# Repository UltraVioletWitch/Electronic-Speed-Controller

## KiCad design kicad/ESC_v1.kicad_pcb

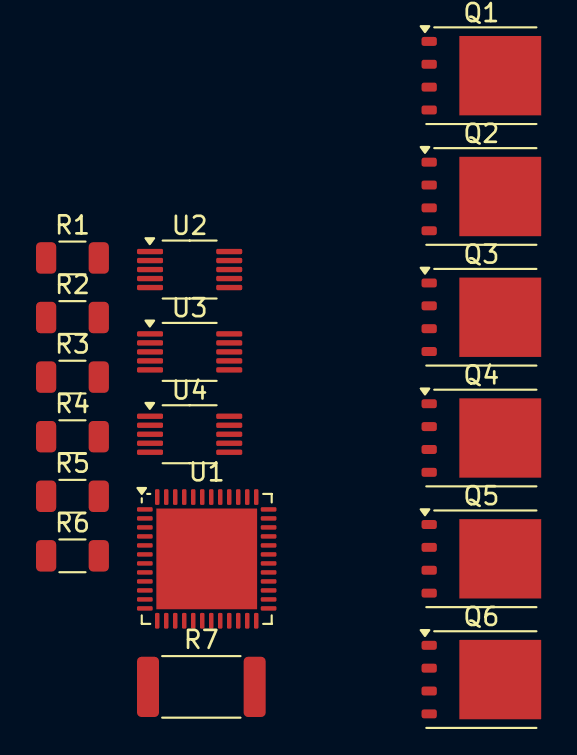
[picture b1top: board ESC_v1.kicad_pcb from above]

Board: 2 copper layers, 17 parts (0 on the bottom side), 19 nets, no tracks yet.

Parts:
Q1, Q2, Q3, Q4, Q5, Q6: CSD17573Q5B; TDSON-8-1
R1, R2, R3, R4, R5, R6: 1; R_1206_3216Metric
R7: 1m; R_2512_6332Metric
U1: STM32H503CBUx; QFN-48-1EP_7x7mm_P0.5mm_EP5.6x5.6mm
U2, U3, U4: LM5106MMX; VSSOP-10_3x3mm_P0.5mm

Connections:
+BATT: Q1.5 (D), Q3.5 (D), Q5.5 (D)
GND: R7.2, U1.8 (VSSA), U1.23 (VSS), U1.35 (VSS), U1.47 (VSS), U1.49 (VSS)
I_SENSE: Q2.1 (S), Q2.2 (S), Q2.3 (S), Q4.1 (S), Q4.2 (S), Q4.3 (S), Q6.1 (S), Q6.2 (S), Q6.3 (S), R7.1
unnamed: Q1.4 (G), R1.2
unnamed: Q2.4 (G), R2.2
unnamed: Q3.4 (G), R3.2
unnamed: Q4.4 (G), R4.2
unnamed: Q5.4 (G), R5.2
unnamed: Q6.4 (G), R6.2
unnamed: R1.1, U2.4 (HS)
unnamed: R2.1, U2.10 (LO)
unnamed: R3.1, U3.4 (HS)
unnamed: R4.1, U3.10 (LO)
unnamed: R5.1, U4.4 (HS)
unnamed: R6.1, U4.10 (LO)
PHASE_X: Q1.1 (S), Q1.2 (S), Q1.3 (S), Q2.5 (D)
PHASE_Y: Q3.1 (S), Q3.2 (S), Q3.3 (S), Q4.5 (D)
PHASE_Z: Q5.1 (S), Q5.2 (S), Q5.3 (S), Q6.5 (D)
VCC: U1.1 (VBAT), U1.9 (VDDA), U1.24 (VDD), U1.36 (VDD), U1.48 (VDD)

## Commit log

2026-04-22 removed redundant ESC_v1 folder
2026-04-22 fixed parts library
